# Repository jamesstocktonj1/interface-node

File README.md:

# Garden Interface Node

## Hardware
The hardware is based around the Pi Pico. It simply has 2x RS485 interfaces to independent Serial ports. It also has a range of status LEDs to do with flow control and the bus status.

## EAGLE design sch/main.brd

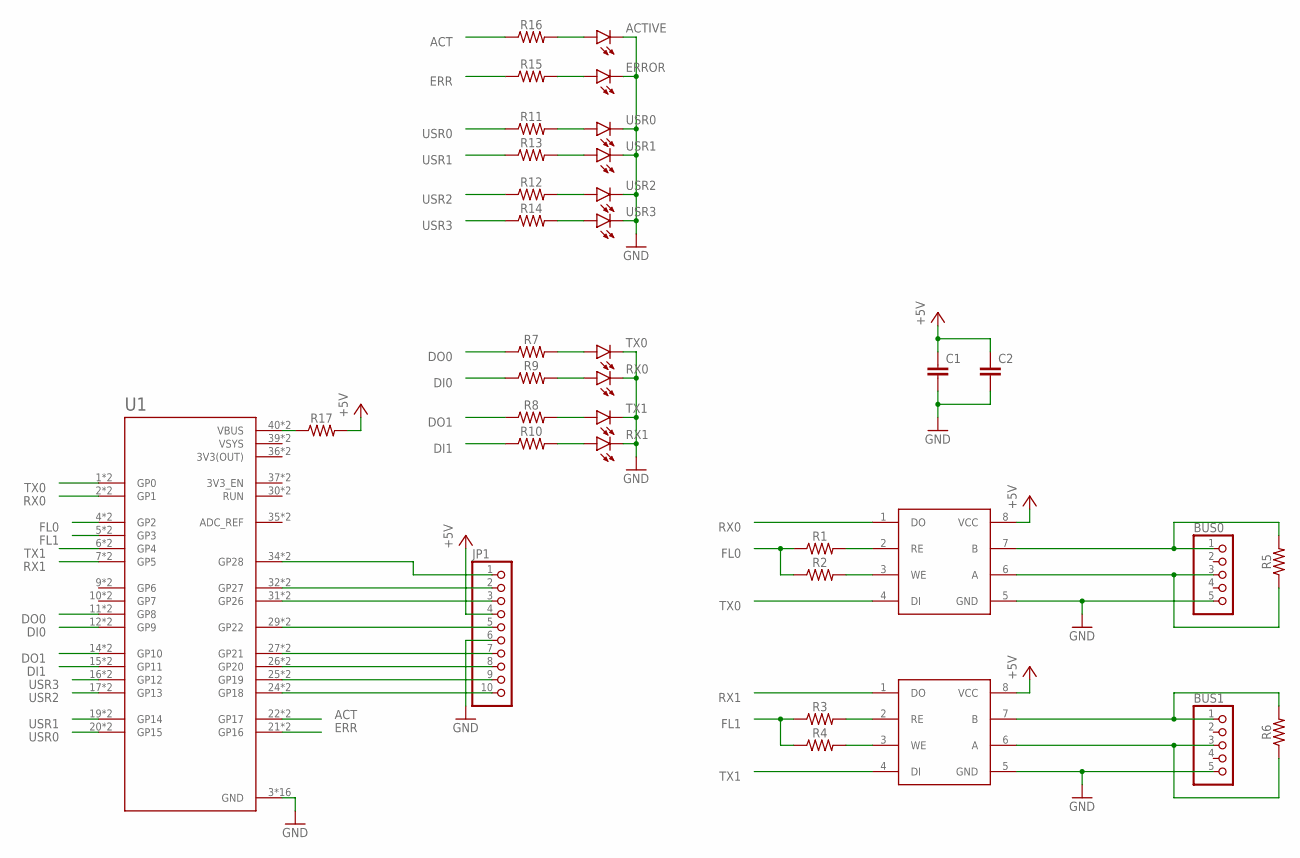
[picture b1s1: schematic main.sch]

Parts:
ACTIVE: LED0603; LED-0603
BUS0, BUS1: PINHD-1X5; 1X05
C1, C2: CAP-0603; 0603
ERROR: LED0603; LED-0603
JP1: PINHD-1X10; 1X10
R1, R2, R3, R4, R5, R6, R7, R8, R9, R10, R11, R12, R13, R14, R15, R16, R17: 0603
RX0, RX1: LED0603; LED-0603
TX0, TX1: LED0603; LED-0603
U1: RASPBERRY_PICO-NO_DEBUG; PICO-PKG-NO_DEBUG
U$1, U$2: MAX485; SO8
USR0, USR1, USR2, USR3: LED0603; LED-0603

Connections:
3V3(OUT): U1.36 (3V3(OUT)), U1.P$36 (3V3(OUT))
+5V: C1.1, C2.1, JP1.4, R17.2, U$1.8 (VCC), U$2.8 (VCC)
ACT: R16.1, U1.22 (GP17), U1.P$22 (GP17)
DI0: R9.1, U1.12 (GP9), U1.P$12 (GP9)
DI1: R10.1, U1.15 (GP11), U1.P$15 (GP11)
DO0: R7.1, U1.11 (GP8), U1.P$11 (GP8)
DO1: R8.1, U1.14 (GP10), U1.P$14 (GP10)
ERR: R15.1, U1.21 (GP16), U1.P$21 (GP16)
FL0: R1.1, R2.1, U1.4 (GP2), U1.P$4 (GP2)
FL1: R3.1, R4.1, U1.5 (GP3), U1.P$5 (GP3)
GND: ACTIVE.C, BUS0.5, BUS1.5, C1.2, C2.2, ERROR.C, JP1.6, RX0.C, RX1.C, TX0.C, TX1.C, U1.3 (GND), U1.8 (GND), U1.13 (GND), U1.18 (GND), U1.23 (GND), U1.28 (GND), U1.33 (GND), U1.38 (GND), U1.P$3 (GND), U1.P$8 (GND), U1.P$13 (GND), U1.P$18 (GND), U1.P$23 (GND), U1.P$28 (GND), U1.P$33 (GND), U1.P$38 (GND), U$1.5 (GND), U$2.5 (GND), USR0.C, USR1.C, USR2.C, USR3.C
unnamed: BUS0.1, R5.2, U$1.7 (B)
unnamed: BUS0.3, R5.1, U$1.6 (A)
unnamed: BUS1.1, R6.2, U$2.7 (B)
unnamed: BUS1.3, R6.1, U$2.6 (A)
unnamed: R1.2, U$1.2 (RE)
unnamed: R2.2, U$1.3 (WE)
unnamed: R3.2, U$2.2 (RE)
unnamed: R4.2, U$2.3 (WE)
unnamed: R11.2, USR0.A
unnamed: R7.2, TX0.A
unnamed: R9.2, RX0.A
unnamed: R8.2, TX1.A
unnamed: R10.2, RX1.A
unnamed: R13.2, USR1.A
unnamed: R12.2, USR2.A
unnamed: R14.2, USR3.A
unnamed: ERROR.A, R15.2
unnamed: ACTIVE.A, R16.2
unnamed: JP1.10, U1.24 (GP18), U1.P$24 (GP18)
unnamed: JP1.9, U1.25 (GP19), U1.P$25 (GP19)
unnamed: JP1.8, U1.26 (GP20), U1.P$26 (GP20)
unnamed: JP1.7, U1.27 (GP21), U1.P$27 (GP21)
unnamed: JP1.5, U1.29 (GP22), U1.P$29 (GP22)
unnamed: JP1.3, U1.31 (GP26), U1.P$31 (GP26)
unnamed: JP1.2, U1.32 (GP27), U1.P$32 (GP27)
unnamed: JP1.1, U1.34 (GP28), U1.P$34 (GP28)
unnamed: R17.1, U1.40 (VBUS), U1.P$40 (VBUS)
RX0: U1.2 (GP1), U1.P$2 (GP1), U$1.1 (DO)
RX1: U1.7 (GP5), U1.P$7 (GP5), U$2.1 (DO)
TX0: U1.1 (GP0), U1.P$1 (GP0), U$1.4 (DI)
TX1: U1.6 (GP4), U1.P$6 (GP4), U$2.4 (DI)
USR0: R11.1, U1.20 (GP15), U1.P$20 (GP15)
USR1: R13.1, U1.19 (GP14), U1.P$19 (GP14)
USR2: R12.1, U1.17 (GP13), U1.P$17 (GP13)
USR3: R14.1, U1.16 (GP12), U1.P$16 (GP12)
VSYS: U1.39 (VSYS), U1.P$39 (VSYS)

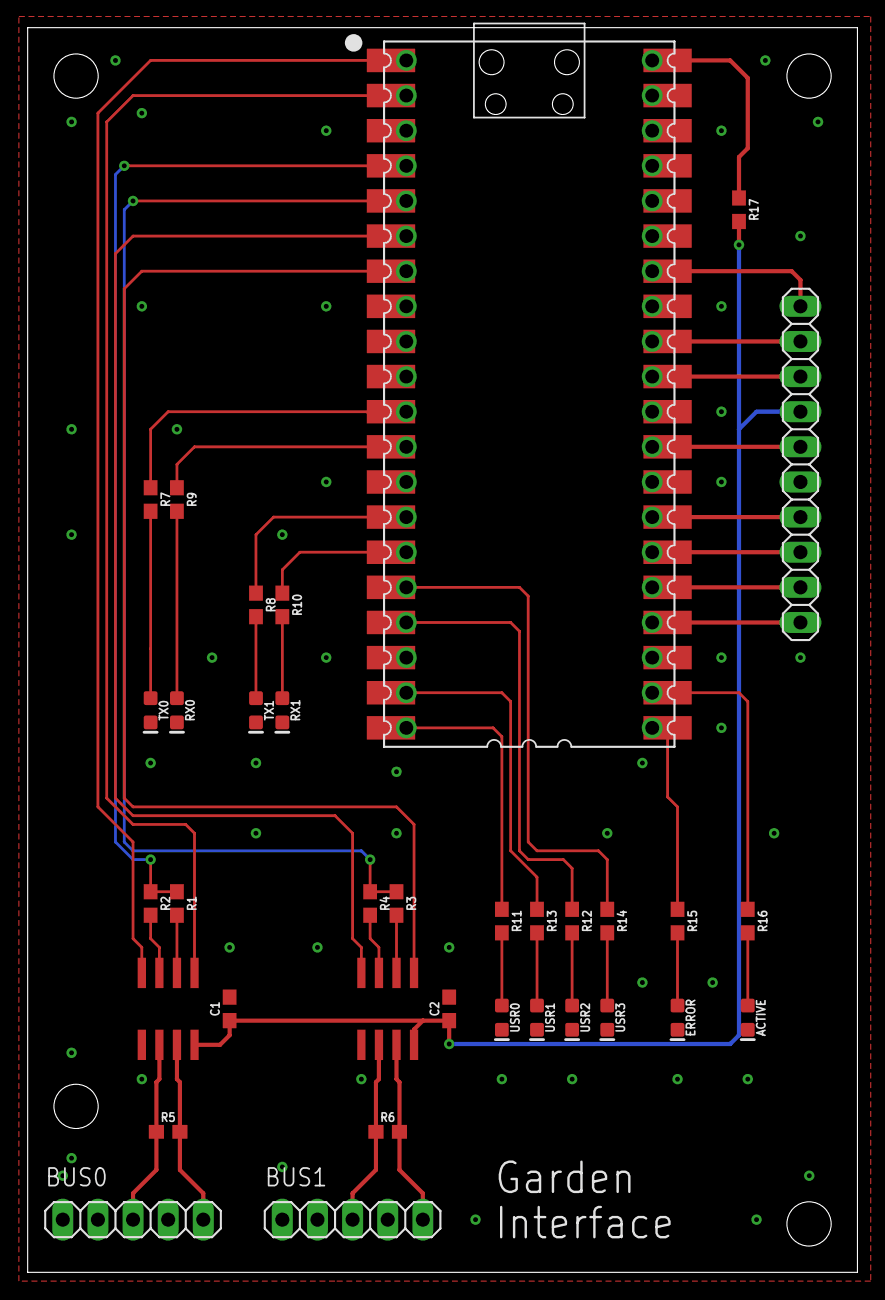
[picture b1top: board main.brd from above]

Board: 2 copper layers, 60.0 x 90.0 mm, 35 parts (0 on the bottom side), 47 nets.

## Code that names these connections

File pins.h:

// pin definition file


// Interface 1
#define TX1         0
#define RX1         1
#define FL1         2

// Interface 2
#define TX2         4
#define RX2         5
#define FL2         3

// Interface LEDs
#define TXLED1      8
#define RXLED1      9
#define TXLED2      10
#define RXLED2      11

// User LEDs
#define USR0        15
#define USR1        14
#define USR2        13
#define USR3        12
int user_led[4] =   {USR0, USR1, USR2, USR3};

// Activity LEDs
#define ACT         17
#define ERR         16

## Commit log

2022-07-28 Add gitignore
2022-07-28 Initial Push
2022-07-28 Create comms
2022-07-28 Basic Serial
2022-07-28 Add Com States
2022-07-28 Add Serial Read
2022-07-28 Add Board Files
2022-07-28 Add Input Buffer
2022-07-30 Add State Based Flow Control
2022-07-30 Fix Flow Control
2022-07-30 Add Comms Timeout
2022-07-30 Add Led Reset on Timeout
2022-07-30 Add Status LED
2022-07-30 Fix Status LED
2022-08-21 Fix Clear Write Buffer / Refactor
2022-08-21 Refactor Code
2022-08-21 Add Initial Bus Monitor

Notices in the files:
parts and their libraries:
SparkFun-Resistors: Licensing: Creative Commons ShareAlike 4.0 International - https://creativecommons.org/licenses/by-sa/4.0
